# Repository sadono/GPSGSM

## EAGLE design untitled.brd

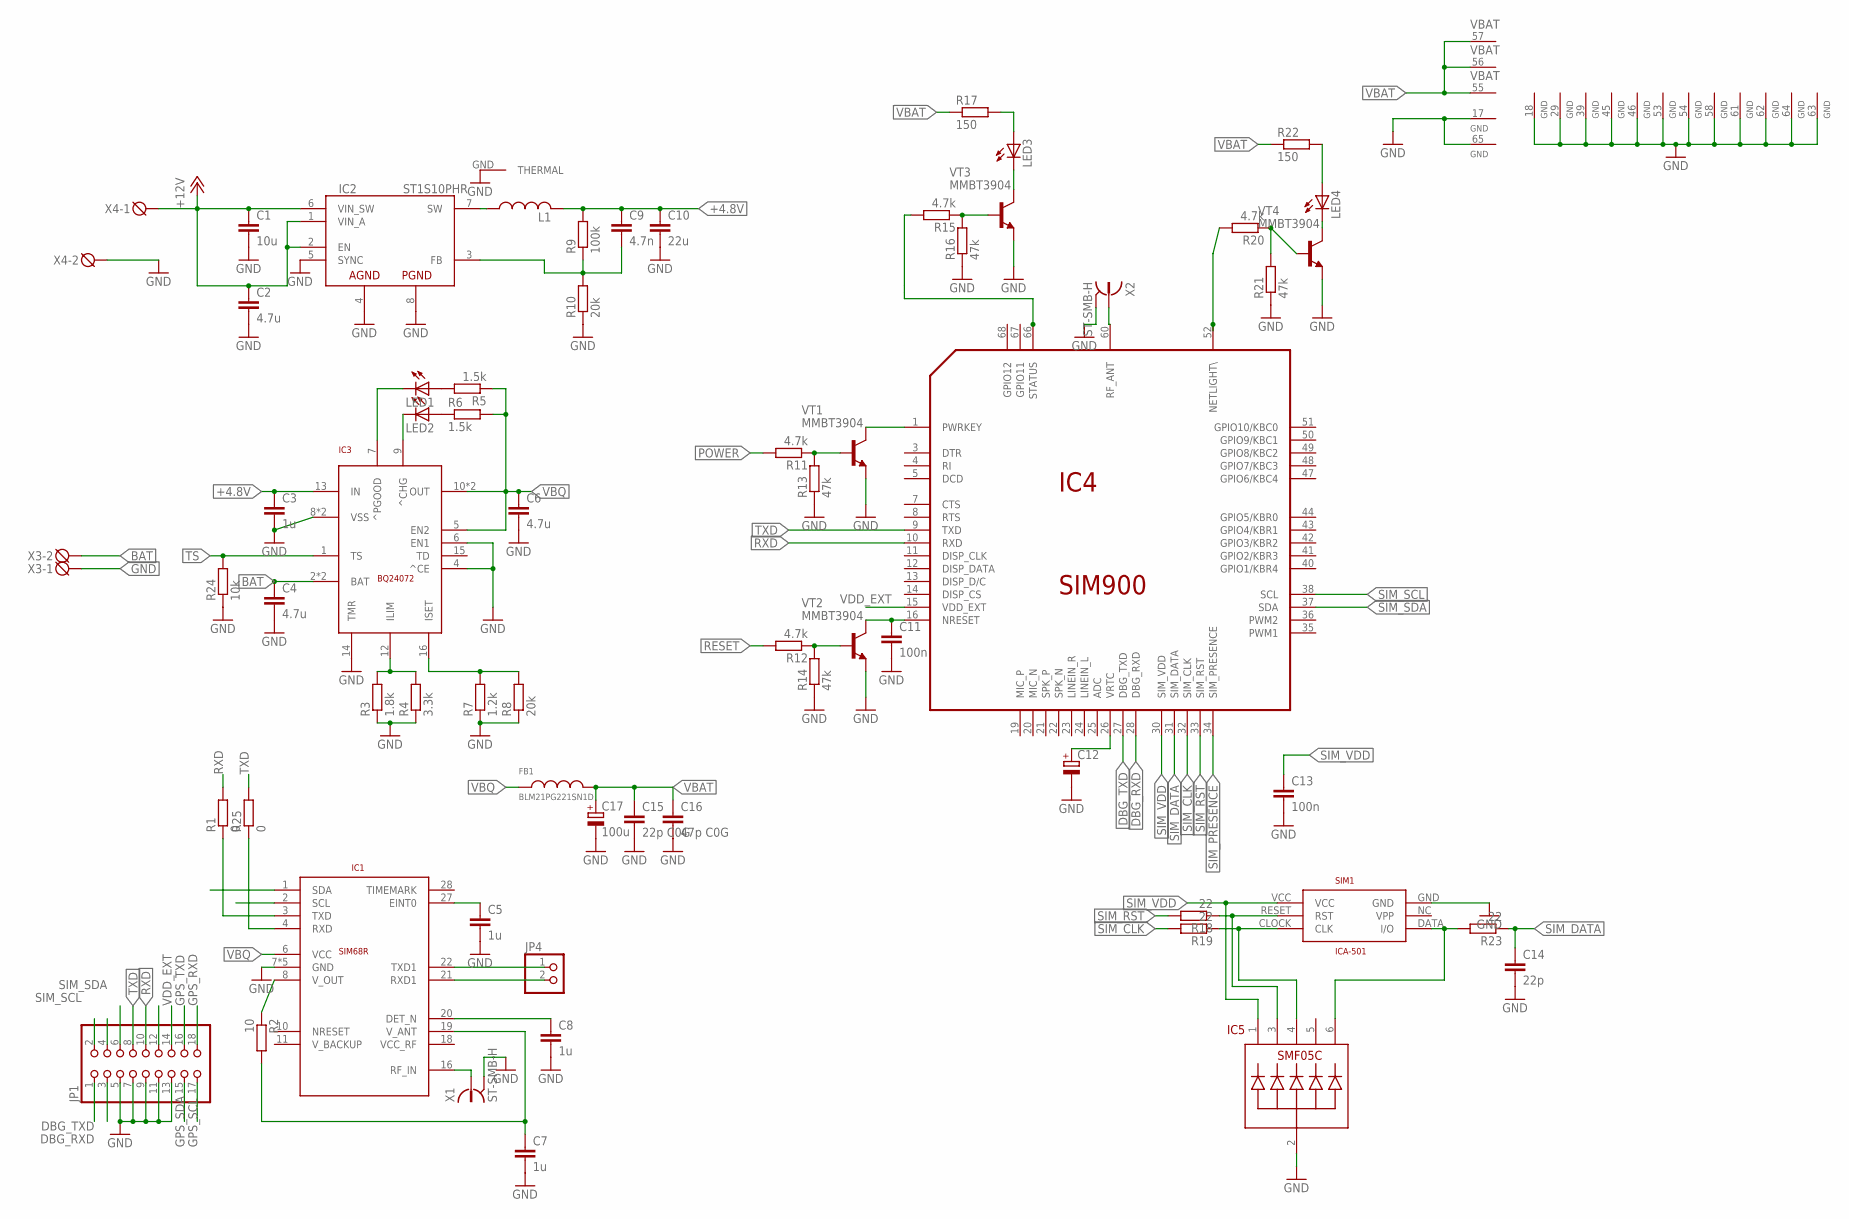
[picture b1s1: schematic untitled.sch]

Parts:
C1: 10u; C0805
C2, C4, C6: 4.7u; C0805
C3, C5, C7, C8: 1u; C0805
C9: 4.7n; C0805
C10: 22u; C0805
C11, C13: 100n; C0805
C12: CPOL-EUA/3216-18R; A/3216-18R
C14: 22p; C0805
C15: 22p C0G; C0805
C16: 47p C0G; C0805
C17: 100u; B/3528-21W
FB1: BLM21PG221SN1D; R0805
IC1: SIM68R; SIM68
IC2: ST1S10PHR; HSOP8
IC3: BQ24072; QFN16
IC4: SIM900
IC5: SMF05C; SC-70-6
JP1: PINHD-2X9; 2X09
JP4: PINHD-1X2ROUND; 1X02ROUND
L1: INDUCTOR-SUMIDA-CDRH4D18
LED1, LED2, LED3, LED4: LED0805; SML0805
R1, R25: 0; R0805
R2: 10; R0805
R3: 1.8k; R0805
R4: 3.3k; R0805
R5, R6: 1.5k; R0603
R7: 1.2k; R0603
R8, R10: 20k; R0805
R9: 100k; R0805
R11, R12, R15, R20: 4.7k; R0805
R13, R14, R16, R21: 47k; R0805
R17, R22: 150; R0805
R18, R19, R23: 22; R0805
R24: 10k; R0805
SIM1: ICA-501; ICA-501-006-F7
VT1, VT2, VT3, VT4: MMBT3904; SOT23-BCE
X1, X2: ST-SMB-H
X3, X4: DG3XX-02-5.0; DG306-5.0-02P

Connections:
+4.8V: C3.1, C9.1, C10.1, IC3.13 (IN), L1.P$2, R9.2
+12V: C1.1, C2.1, IC2.1 (VIN_A), IC2.2 (EN), IC2.6 (VIN_SW), X4.1
BAT: C4.1, IC3.2 (BAT), IC3.3 (BAT), X3.2
DBG_RXD: IC4.28 (DBG_RXD), JP1.3
DBG_TXD: IC4.27 (DBG_TXD), JP1.1
GND: C1.2, C2.2, C3.2, C4.2, C5.2, C6.2, C7.2, C8.2, C10.2, C11.2, C12.-, C13.2, C14.2, C15.2, C16.2, C17.-, IC1.7 (GND), IC1.13 (GND), IC1.14 (GND), IC1.15 (GND), IC1.17 (GND), IC2.4 (AGND), IC2.5 (SYNC), IC2.8 (PGND), IC2.GND (THERMAL), IC3.4 (^CE), IC3.6 (EN1), IC3.8 (VSS), IC3.14 (TMR), IC3.TH (VSS), IC4.17 (GND), IC4.18 (GND), IC4.29 (GND), IC4.39 (GND), IC4.45 (GND), IC4.46 (GND), IC4.53 (GND), IC4.54 (GND), IC4.58 (GND), IC4.59 (GND), IC4.61 (GND), IC4.62 (GND), IC4.63 (GND), IC4.64 (GND), IC4.65 (GND), IC5.2, JP1.5, JP1.7, JP1.9, JP1.11, JP1.13, R3.1, R4.1, R7.1, R8.1, R10.1, R13.1, R14.1, R16.1, R21.1, R24.1, SIM1.GND, VT1.E, VT2.E, VT3.E, VT4.E, X1.2, X1.3 (2), X1.4 (2), X1.5 (2), X2.2, X2.3 (2), X2.4 (2), X2.5 (2), X3.1, X4.2
GPS_RXD: IC1.4 (RXD), JP1.18, R25.1
GPS_SCL: IC1.2 (SCL), JP1.17
GPS_SDA: IC1.1 (SDA), JP1.15
GPS_TXD: IC1.3 (TXD), JP1.16, R1.1
unnamed: IC2.7 (SW), L1.P$1
unnamed: C11.1, IC4.16 (NRESET), VT2.C
unnamed: C9.2, IC2.3 (FB), R9.1, R10.2
unnamed: LED2.A, R6.1
unnamed: IC3.16 (ISET), R7.2, R8.2
unnamed: IC3.12 (ILIM), R3.2, R4.2
unnamed: LED1.A, R5.2
unnamed: IC3.9 (^CHG), LED2.C
unnamed: IC3.7 (^PGOOD), LED1.C
unnamed: IC4.1 (PWRKEY), VT1.C
unnamed: R11.1, R13.2, VT1.B
unnamed: R12.1, R14.2, VT2.B
unnamed: IC4.60 (RF_ANT), X2.1
unnamed: IC5.3, R18.1, SIM1.RESET (RST)
unnamed: IC5.6, R23.2, SIM1.DATA (I/O)
unnamed: LED4.C, VT4.C
unnamed: C12.+, IC4.26 (VRTC)
unnamed: IC5.4, R19.1, SIM1.CLOCK (CLK)
unnamed: R20.1, R21.2, VT4.B
unnamed: IC4.52 (NETLIGHT\), R20.2
unnamed: IC1.8 (V_OUT), R2.1
unnamed: C7.1, IC1.19 (V_ANT), R2.2
unnamed: IC1.16 (RF_IN), X1.1
unnamed: IC1.22 (TXD1), JP4.1
unnamed: C8.1, IC1.20 (DET_N)
unnamed: C5.1, IC1.27 (EINT0)
unnamed: IC1.21 (RXD1), JP4.2
unnamed: R15.1, R16.2, VT3.B
unnamed: LED3.A, R17.2
unnamed: LED3.C, VT3.C
unnamed: IC4.66 (STATUS), R15.2
unnamed: LED4.A, R22.2
POWER: JP1.12, R11.2
RESET: JP1.6, R12.2
RXD: IC4.10 (RXD), JP1.10, R1.2
SIM_CLK: IC4.32 (SIM_CLK), R19.2
SIM_DATA: C14.1, IC4.31 (SIM_DATA), R23.1
SIM_PRESENCE: IC4.34 (SIM_PRESENCE)
SIM_RST: IC4.33 (SIM_RST), R18.2
SIM_SCL: IC4.38 (SCL), JP1.2
SIM_SDA: IC4.37 (SDA), JP1.4
SIM_VDD: C13.1, IC4.30 (SIM_VDD), IC5.1, SIM1.VCC
TS: IC3.1 (TS), R24.2
TXD: IC4.9 (TXD), JP1.8, R25.2
VBAT: C15.1, C16.1, C17.+, FB1.2, IC4.55 (VBAT), IC4.56 (VBAT), IC4.57 (VBAT), R17.1, R22.1
VBQ: C6.1, FB1.1, IC1.6 (VCC), IC3.5 (EN2), IC3.10 (OUT), IC3.11 (OUT), R5.1, R6.2
VDD_EXT: IC4.15 (VDD_EXT), JP1.14

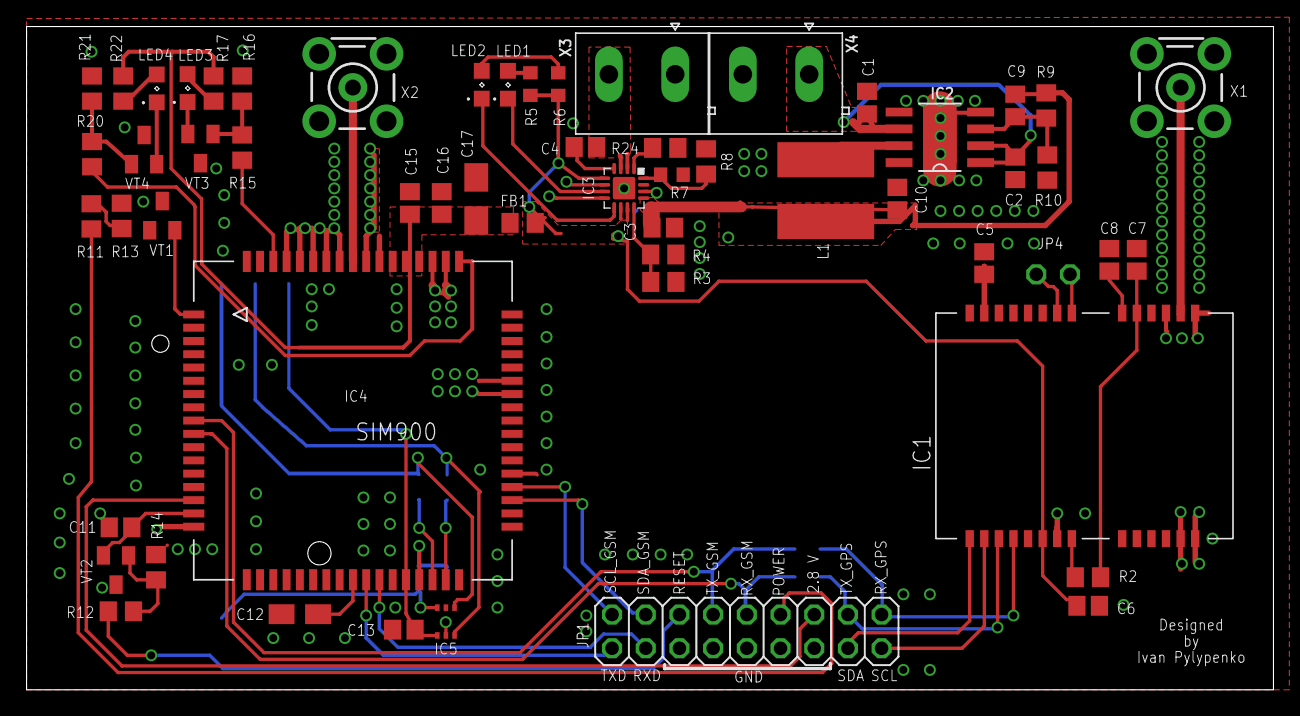
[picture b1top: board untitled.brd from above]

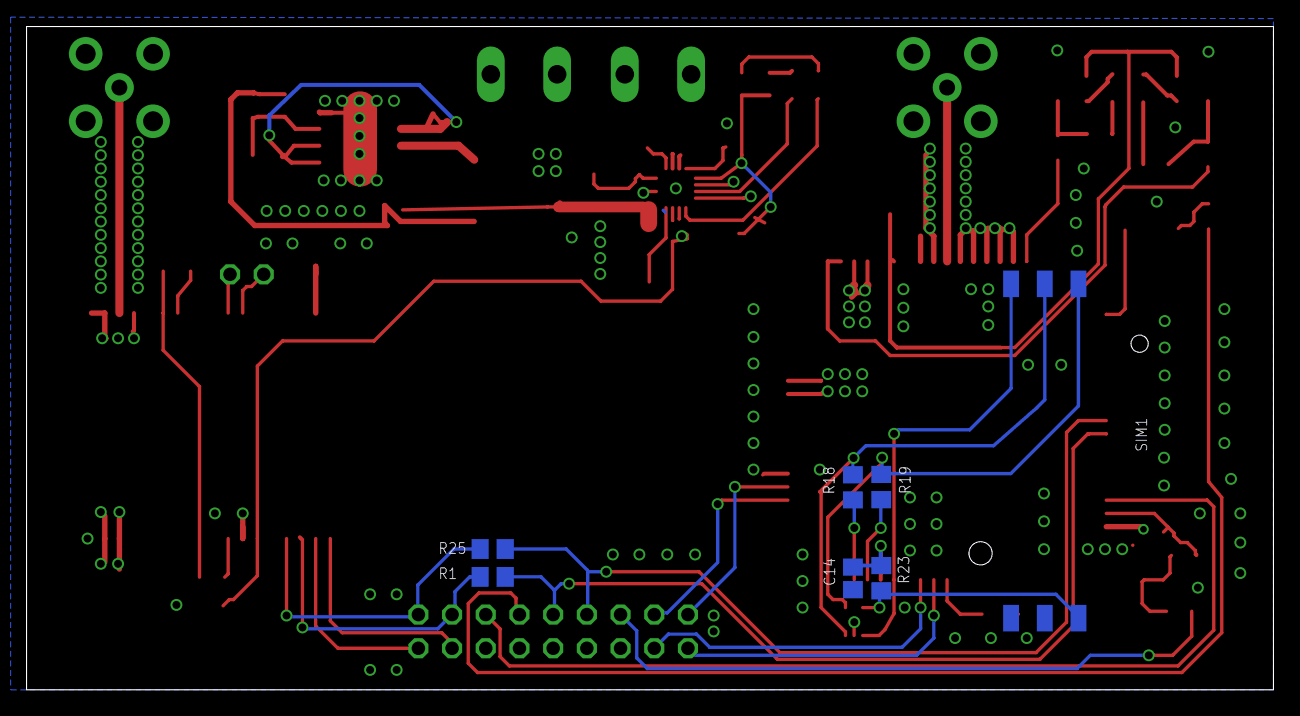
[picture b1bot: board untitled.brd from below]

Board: 2 copper layers, 94.0 x 50.0 mm, 64 parts (7 on the bottom side), 56 nets.

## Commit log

2013-06-24 Two layer GPS/GSM developer board PCB
2013-06-27 Supply changes
    Some traces had been changed in power supply circuit
2013-08-24 Trace changes
    Following items are changed:
    - area between SIM900R and SIM68R footprints is restricted for placing
    traces;
    - some small changes in polygons around SIM900R;
2013-08-24 ST1S10 layout
    Supply component's location has been changed due to ST1S10 datasheet
    layout considerations
2013-10-17 SeedStudio preparation
    GSM fotprint, polygons, thermals
2013-10-18 BQ now on the top
2013-10-24 Silkscreen issues solved
2013-11-24 small changes
2014-05-15 New revision
    Power supply moved to the top.
    IO consolidated
2014-05-25 Production ready version
2014-05-28 Ready for production

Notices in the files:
parts and their libraries:
vreg-pulse: 2009 Draw by Ivan A-R. License CC-BY-SA 3.0
